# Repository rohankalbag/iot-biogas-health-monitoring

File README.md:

# IoT-based Biogas Plant Health Monitoring
 
## EE-344 : Electronics Design Lab

- *An IoT-based monitoring system for a biogas plant that measures and displays parameters such as gas concentrations, humidity, and temperature* 

- *The design consists of a tailor-made custom in-house designed two-layer printed circuit board interfacing gas sensors in a modular fashion using I2C*

- *The data is sent to a central server and stored in a cloud database for remote access and analysis through a web application. The system helps optimize biogas production, identify issues, improve safety, and offers flexibility to integrate additional gas sensors. Furthermore, we successfully addressed anticipated problems during development and prototyping stages and submitted a complete market-ready product*

## [Link to Video Demonstrations](https://youtube.com/playlist?list=PLU3_Wxvmc-mbm3Yfq669lL-GAWkqmuRJW)

## [Link to Detailed Report](https://github.com/rohankalbag/iot-biogas-health-monitoring/blob/chusaro/Report.pdf)

## Recipient of "Best Project Award"

## Contributors : Team TUE-23 : Project 18
- Jujhaar Singh
- Sankalp Bhamare
- Rohan Rajesh Kalbag

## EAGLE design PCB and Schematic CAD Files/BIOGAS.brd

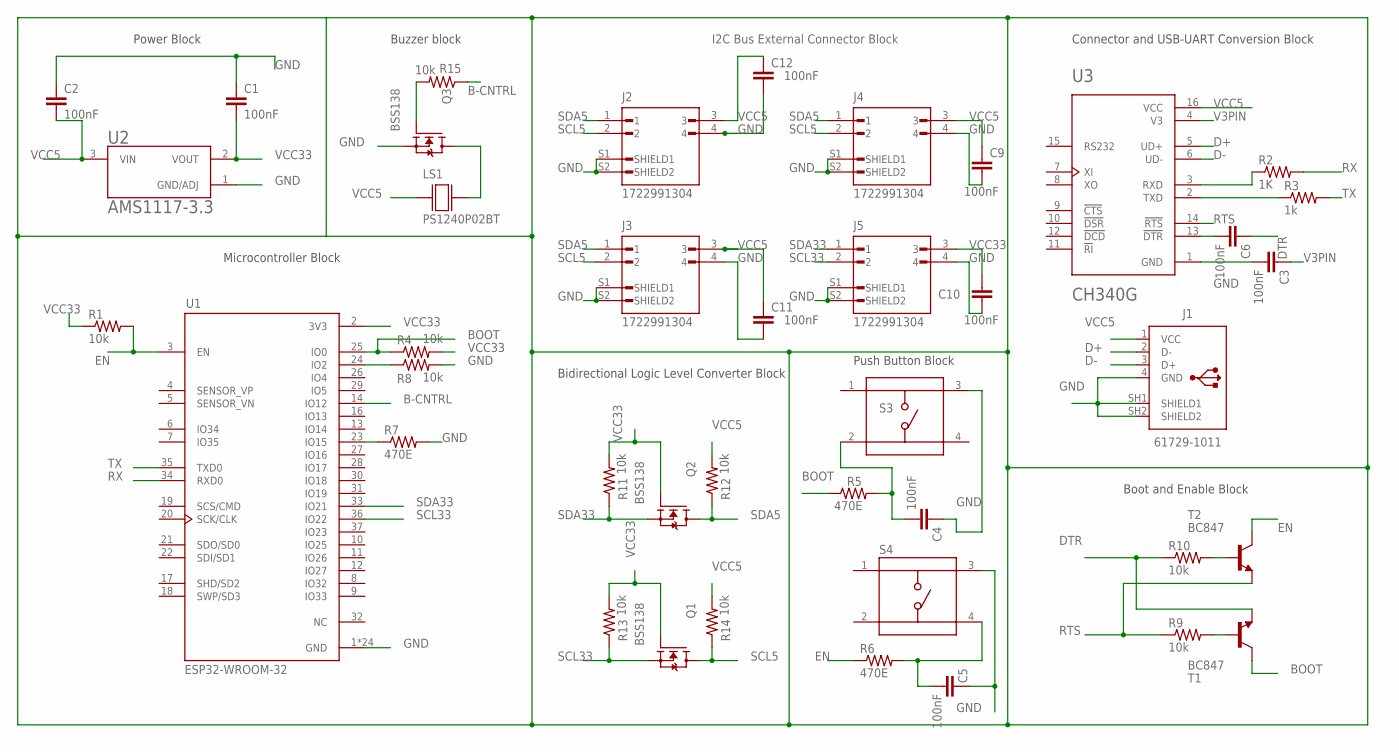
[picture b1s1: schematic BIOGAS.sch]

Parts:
C1, C2, C3, C4, C5, C6, C9, C10, C11, C12: 100nF; C1206
J1: 61729-1011; 61729-1011BLF
J2, J3, J4, J5: 1722991304; MOLEX_1722991304
LS1: PS1240P02BT; XDCR_PS1240P02BT
Q1, Q2, Q3: BSS138; SOT95P240X111-3N
R1, R4, R8, R9, R10, R11, R12, R13, R14, R15: 10k; M1206
R2: 1K; M1206
R3: 1k; M1206
R5, R6, R7: 470E; M1206
S3, S4: TS04-66-55-BK-260-SMT; SW_TS04-66-55-BK-260-SMT
T1, T2: BC847; SOT23
U1: ESP32-WROOM-32; MODULE_ESP32-WROOM-32
U2: AMS1117-3.3; SOT229P700X180-4N
U3: CH340G; SOIC127P600X180-16N

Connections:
B-CNTRL: R15.1, U1.14 (IO12)
BOOT: R4.1, R5.1, T1.3 (C), U1.25 (IO0)
D+: J1.2 (D-), U3.5 (UD+)
D-: J1.3 (D+), U3.6 (UD-)
DTR: C6.1, R10.1, T1.2 (E)
EN: R1.2, R6.1, T2.3 (C), U1.3 (EN)
GND: C1.1, C2.1, C3.2, C4.1, C5.1, C9.2, C10.2, C11.2, C12.2, J1.4 (GND), J1.SH1 (SHIELD1), J1.SH2 (SHIELD2), J2.4, J2.S1 (SHIELD1), J2.S2 (SHIELD2), J3.4, J3.S1 (SHIELD1), J3.S2 (SHIELD2), J4.4, J4.S1 (SHIELD1), J4.S2 (SHIELD2), J5.4, J5.S1 (SHIELD1), J5.S2 (SHIELD2), Q3.2 (S), R7.2, R8.2, S3.3, S4.3, U1.1 (GND), U1.15 (GND), U1.38 (GND), U1.39_1 (GND), U1.39_2 (GND), U1.39_3 (GND), U1.39_4 (GND), U1.39_5 (GND), U1.39_6 (GND), U1.39_7 (GND), U1.39_8 (GND), U1.39_9 (GND), U1.39_10 (GND), U1.39_11 (GND), U1.39_12 (GND), U1.39_13 (GND), U1.39_14 (GND), U1.39_15 (GND), U1.39_16 (GND), U1.39_17 (GND), U1.39_18 (GND), U1.39_19 (GND), U1.39_20 (GND), U1.39_21 (GND), U2.1 (GND/ADJ), U3.1 (GND)
unnamed: R8.1, U1.24 (IO2)
unnamed: R2.1, U3.3 (RXD)
unnamed: R3.1, U3.2 (TXD)
unnamed: C4.2, R5.2, S3.2
unnamed: C5.2, R6.2, S4.4
unnamed: R7.1, U1.23 (IO15)
unnamed: C6.2, U3.13 (!DTR)
unnamed: R10.2, T2.1 (B)
unnamed: R9.2, T1.1 (B)
unnamed: LS1.2, Q3.3 (D)
unnamed: Q3.1 (G), R15.2
RTS: R9.1, T2.2 (E), U3.14 (!RTS)
RX: R2.2, U1.34 (RXD0)
SCL5: J2.2, J3.2, J4.2, Q1.3 (D), R14.1
SCL33: J5.2, Q1.2 (S), R13.1, U1.36 (IO22)
SDA5: J2.1, J3.1, J4.1, Q2.3 (D), R12.1
SDA33: J5.1, Q2.2 (S), R11.1, U1.33 (IO21)
TX: R3.2, U1.35 (TXD0)
V3PIN: C3.1, U3.4 (V3)
VCC5: C2.2, C9.1, C11.1, C12.1, J1.1 (VCC), J2.3, J3.3, J4.3, LS1.1, R12.2, R14.2, U2.3 (VIN), U3.16 (VCC)
VCC33: C1.2, C10.1, J5.3, Q1.1 (G), Q2.1 (G), R1.1, R4.2, R11.2, R13.2, U1.2 (3V3), U2.2 (VOUT)

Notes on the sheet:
Bidirectional Logic Level Converter Block
Boot and Enable Block
Connector and USB-UART Conversion Block
I2C Bus External Connector Block
Power Block
Microcontroller Block
Push Button Block
Buzzer block

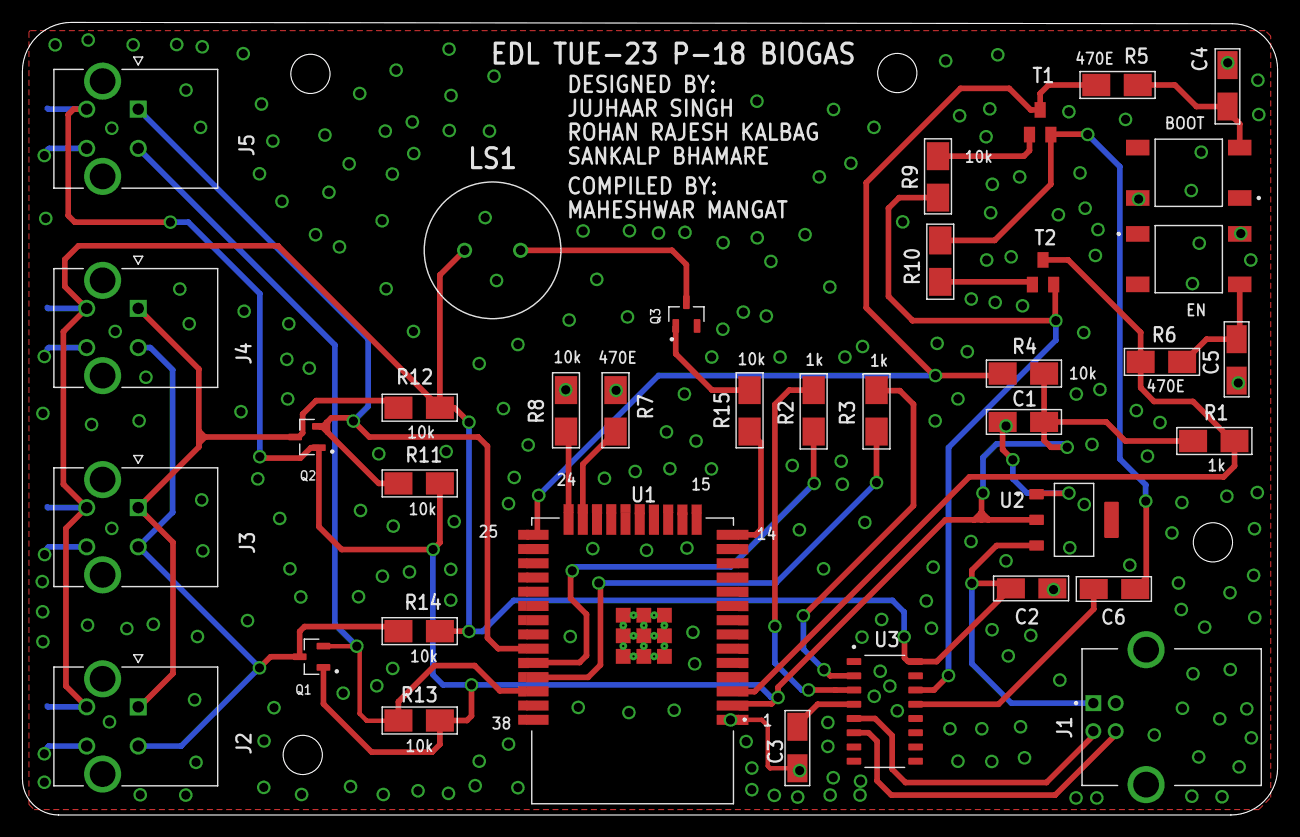
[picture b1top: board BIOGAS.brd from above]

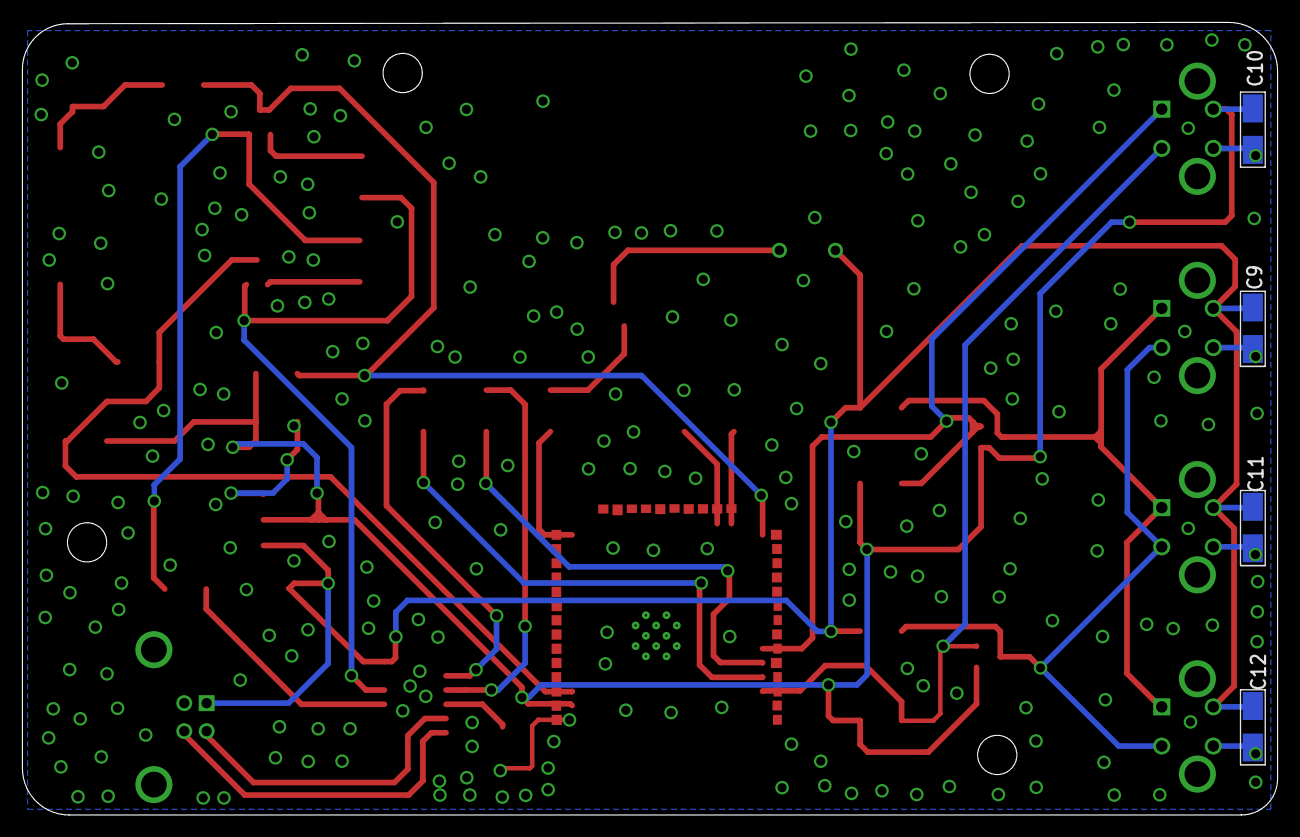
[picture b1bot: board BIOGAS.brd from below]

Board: 2 copper layers, 112.0 x 70.7 mm, 41 parts (4 on the bottom side), 28 nets.

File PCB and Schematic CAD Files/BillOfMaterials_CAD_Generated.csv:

"Part";"Value";"Device";"Package";"Description";"AVAILABILITY";"CATEGORY";"CONTACTS";"CURRENT_RATING";"DESCRIPTION";"GENDER";"MANUFACTURER";"MAXIMUM_PACKAGE_HEIGHT";"MF";"MOUNT_TYPE";"MP";"MPN";"OPERATING_TEMP";"PACKAGE";"PARTREV";"PART_STATUS";"PRICE";"ROHS_COMPLIANT";"SERIES";"SNAPEDA_PACKAGE_ID";"SNAPEDA_PN";"STANDARD";"SUB-CATEGORY";"TYPE";"VOLTAGE_RATING";
"C1";"100nF";"CAPACITOR_SMD_1206";"C1206";"";"";"";"";"";"";"";"";"";"";"";"";"";"";"";"";"";"";"";"";"";"";"";"";"";"";
"C2";"100nF";"CAPACITOR_SMD_1206";"C1206";"";"";"";"";"";"";"";"";"";"";"";"";"";"";"";"";"";"";"";"";"";"";"";"";"";"";
"C3";"100nF";"CAPACITOR_SMD_1206";"C1206";"";"";"";"";"";"";"";"";"";"";"";"";"";"";"";"";"";"";"";"";"";"";"";"";"";"";
"C4";"100nF";"CAPACITOR_SMD_1206";"C1206";"";"";"";"";"";"";"";"";"";"";"";"";"";"";"";"";"";"";"";"";"";"";"";"";"";"";
"C5";"100nF";"CAPACITOR_SMD_1206";"C1206";"";"";"";"";"";"";"";"";"";"";"";"";"";"";"";"";"";"";"";"";"";"";"";"";"";"";
"C6";"100nF";"CAPACITOR_SMD_1206";"C1206";"";"";"";"";"";"";"";"";"";"";"";"";"";"";"";"";"";"";"";"";"";"";"";"";"";"";
"C9";"100nF";"CAPACITOR_SMD_1206";"C1206";"";"";"";"";"";"";"";"";"";"";"";"";"";"";"";"";"";"";"";"";"";"";"";"";"";"";
"C10";"100nF";"CAPACITOR_SMD_1206";"C1206";"";"";"";"";"";"";"";"";"";"";"";"";"";"";"";"";"";"";"";"";"";"";"";"";"";"";
"C11";"100nF";"CAPACITOR_SMD_1206";"C1206";"";"";"";"";"";"";"";"";"";"";"";"";"";"";"";"";"";"";"";"";"";"";"";"";"";"";
"C12";"100nF";"CAPACITOR_SMD_1206";"C1206";"";"";"";"";"";"";"";"";"";"";"";"";"";"";"";"";"";"";"";"";"";"";"";"";"";"";
"J1";"61729-1011";"61729-1011";"61729-1011BLF";"USB(2.0) Type-B, RCPT, 4POS, THT-R/A";"";"Connector";"4";"1A";"CONN RCPT USB2.0 TYPEB 4POS R/A";"Receptacle";"Amphenol ICC (FCI)";"";"";"R/A";"";"61729-1011BLF";"-55°C to 85°C ";"";"";"Active";"";"RoHS Compliant";"61729";"";"";"";"USB";"USB-B";"";
"J2";"1722991304";"1722991304";"MOLEX_1722991304";"";"";"";"";"";"";"";"Molex";"14.0 mm";"";"";"";"";"";"";"B8";"";"";"";"";"";"";"Manufacturer Recommendations";"";"";"";
"J3";"1722991304";"1722991304";"MOLEX_1722991304";"";"";"";"";"";"";"";"Molex";"14.0 mm";"";"";"";"";"";"";"B8";"";"";"";"";"";"";"Manufacturer Recommendations";"";"";"";
"J4";"1722991304";"1722991304";"MOLEX_1722991304";"";"";"";"";"";"";"";"Molex";"14.0 mm";"";"";"";"";"";"";"B8";"";"";"";"";"";"";"Manufacturer Recommendations";"";"";"";
"J5";"1722991304";"1722991304";"MOLEX_1722991304";"";"";"";"";"";"";"";"Molex";"14.0 mm";"";"";"";"";"";"";"B8";"";"";"";"";"";"";"Manufacturer Recommendations";"";"";"";
"LS1";"PS1240P02BT";"PS1240P02BT";"XDCR_PS1240P02BT";"Buzzers Transducer, Externally Driven Piezo 3V 4kHz 60dB @ 3V, 10cm Through Hole PC Pins";"Unavailable";"";"";"";" Buzzers Transducer, Externally Driven Piezo 3V 4kHz 60dB @ 3V, 10cm Through Hole PC Pins ";"";"";"7.0mm";"TDK";"";"PS1240P02CT3";"";"";"SIP-5 TDK";"";"";"None";"";"";"";"";"";"";"";"";
"Q1";"BSS138";"BSS138";"SOT95P240X111-3N";"N-Channel 50V 220mA (Ta) 360mW (Ta) Surface Mount SOT-23-3";"";"";"";"";"";"";"ON Semiconductor";"1.11 mm";"";"";"";"";"";"";"30 Jan 2018";"";"";"";"";"";"";"IPC 7351B";"";"";"";
"Q2";"BSS138";"BSS138";"SOT95P240X111-3N";"N-Channel 50V 220mA (Ta) 360mW (Ta) Surface Mount SOT-23-3";"";"";"";"";"";"";"ON Semiconductor";"1.11 mm";"";"";"";"";"";"";"30 Jan 2018";"";"";"";"";"";"";"IPC 7351B";"";"";"";
"Q3";"BSS138";"BSS138";"SOT95P240X111-3N";"N-Channel 50V 220mA (Ta) 360mW (Ta) Surface Mount SOT-23-3";"";"";"";"";"";"";"ON Semiconductor";"1.11 mm";"";"";"";"";"";"";"30 Jan 2018";"";"";"";"";"";"";"IPC 7351B";"";"";"";
"R1";"10k";"RESISTOR_SMD_1206";"M1206";"";"";"";"";"";"";"";"";"";"";"";"";"";"";"";"";"";"";"";"";"";"";"";"";"";"";
"R2";"1K";"RESISTOR_SMD_1206";"M1206";"";"";"";"";"";"";"";"";"";"";"";"";"";"";"";"";"";"";"";"";"";"";"";"";"";"";
"R3";"1k";"RESISTOR_SMD_1206";"M1206";"";"";"";"";"";"";"";"";"";"";"";"";"";"";"";"";"";"";"";"";"";"";"";"";"";"";
"R4";"10k";"RESISTOR_SMD_1206";"M1206";"";"";"";"";"";"";"";"";"";"";"";"";"";"";"";"";"";"";"";"";"";"";"";"";"";"";
"R5";"470E";"RESISTOR_SMD_1206";"M1206";"";"";"";"";"";"";"";"";"";"";"";"";"";"";"";"";"";"";"";"";"";"";"";"";"";"";
"R6";"470E";"RESISTOR_SMD_1206";"M1206";"";"";"";"";"";"";"";"";"";"";"";"";"";"";"";"";"";"";"";"";"";"";"";"";"";"";
"R7";"470E";"RESISTOR_SMD_1206";"M1206";"";"";"";"";"";"";"";"";"";"";"";"";"";"";"";"";"";"";"";"";"";"";"";"";"";"";
"R8";"10k";"RESISTOR_SMD_1206";"M1206";"";"";"";"";"";"";"";"";"";"";"";"";"";"";"";"";"";"";"";"";"";"";"";"";"";"";
"R9";"10k";"RESISTOR_SMD_1206";"M1206";"";"";"";"";"";"";"";"";"";"";"";"";"";"";"";"";"";"";"";"";"";"";"";"";"";"";
"R10";"10k";"RESISTOR_SMD_1206";"M1206";"";"";"";"";"";"";"";"";"";"";"";"";"";"";"";"";"";"";"";"";"";"";"";"";"";"";
"R11";"10k";"RESISTOR_SMD_1206";"M1206";"";"";"";"";"";"";"";"";"";"";"";"";"";"";"";"";"";"";"";"";"";"";"";"";"";"";
"R12";"10k";"RESISTOR_SMD_1206";"M1206";"";"";"";"";"";"";"";"";"";"";"";"";"";"";"";"";"";"";"";"";"";"";"";"";"";"";
"R13";"10k";"RESISTOR_SMD_1206";"M1206";"";"";"";"";"";"";"";"";"";"";"";"";"";"";"";"";"";"";"";"";"";"";"";"";"";"";
"R14";"10k";"RESISTOR_SMD_1206";"M1206";"";"";"";"";"";"";"";"";"";"";"";"";"";"";"";"";"";"";"";"";"";"";"";"";"";"";
"R15";"10k";"RESISTOR_SMD_1206";"M1206";"";"";"";"";"";"";"";"";"";"";"";"";"";"";"";"";"";"";"";"";"";"";"";"";"";"";
"S3";"TS04-66-55-BK-260-SMT";"TS04-66-55-BK-260-SMT";"SW_TS04-66-55-BK-260-SMT";"";"";"";"";"";"";"";"CUI Devices";"";"";"";"";"";"";"";"1.0";"";"";"";"";"";"";"Manufacturer Recommendations";"";"";"";
"S4";"TS04-66-55-BK-260-SMT";"TS04-66-55-BK-260-SMT";"SW_TS04-66-55-BK-260-SMT";"";"";"";"";"";"";"";"CUI Devices";"";"";"";"";"";"";"";"1.0";"";"";"";"";"";"";"Manufacturer Recommendations";"";"";"";
"T1";"BC847";"BC847";"SOT23";"NPN TRANSISTOR";"";"";"";"";"";"";"";"";"";"";"";"";"";"";"";"";"";"";"";"";"";"";"";"";"";
"T2";"BC847";"BC847";"SOT23";"NPN TRANSISTOR";"";"";"";"";"";"";"";"";"";"";"";"";"";"";"";"";"";"";"";"";"";"";"";"";"";
"U1";"ESP32-WROOM-32";"ESP32-WROOM-32";"MODULE_ESP32-WROOM-32";"";"";"";"";"";"";"";"Espressif Systems";"3.2 mm";"";"";"";"";"";"";"2.9";"";"";"";"";"";"";"Manufacturer Recommendations";"";"";"";
"U2";"AMS1117-3.3";"AMS1117-3.3";"SOT229P700X180-4N";"";"";"";"";"";"";"";"Advanced Monolithic Systems";"1.8 mm";"";"";"";"";"";"";"N/A";"";"";"";"";"71280";"AMS1117-3.3";"IPC 7351B";"";"";"";
"U3";"CH340G";"CH340G";"SOIC127P600X180-16N";"";"";"";"";"";"";"";"WCH";"1.8 mm";"";"";"";"";"";"";"2G";"";"";"";"";"";"";"IPC 7351B";"";"";"";

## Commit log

2023-05-20 added documentation
2023-05-20 Updated Documentation
